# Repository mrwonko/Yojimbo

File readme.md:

# Yojimbo

A Ronin with a new master.

For now, this is just a [work log](log.md) and in-progress designs for a USB-C Probe PCB. I know very little about PCB design, so probably don't use this.

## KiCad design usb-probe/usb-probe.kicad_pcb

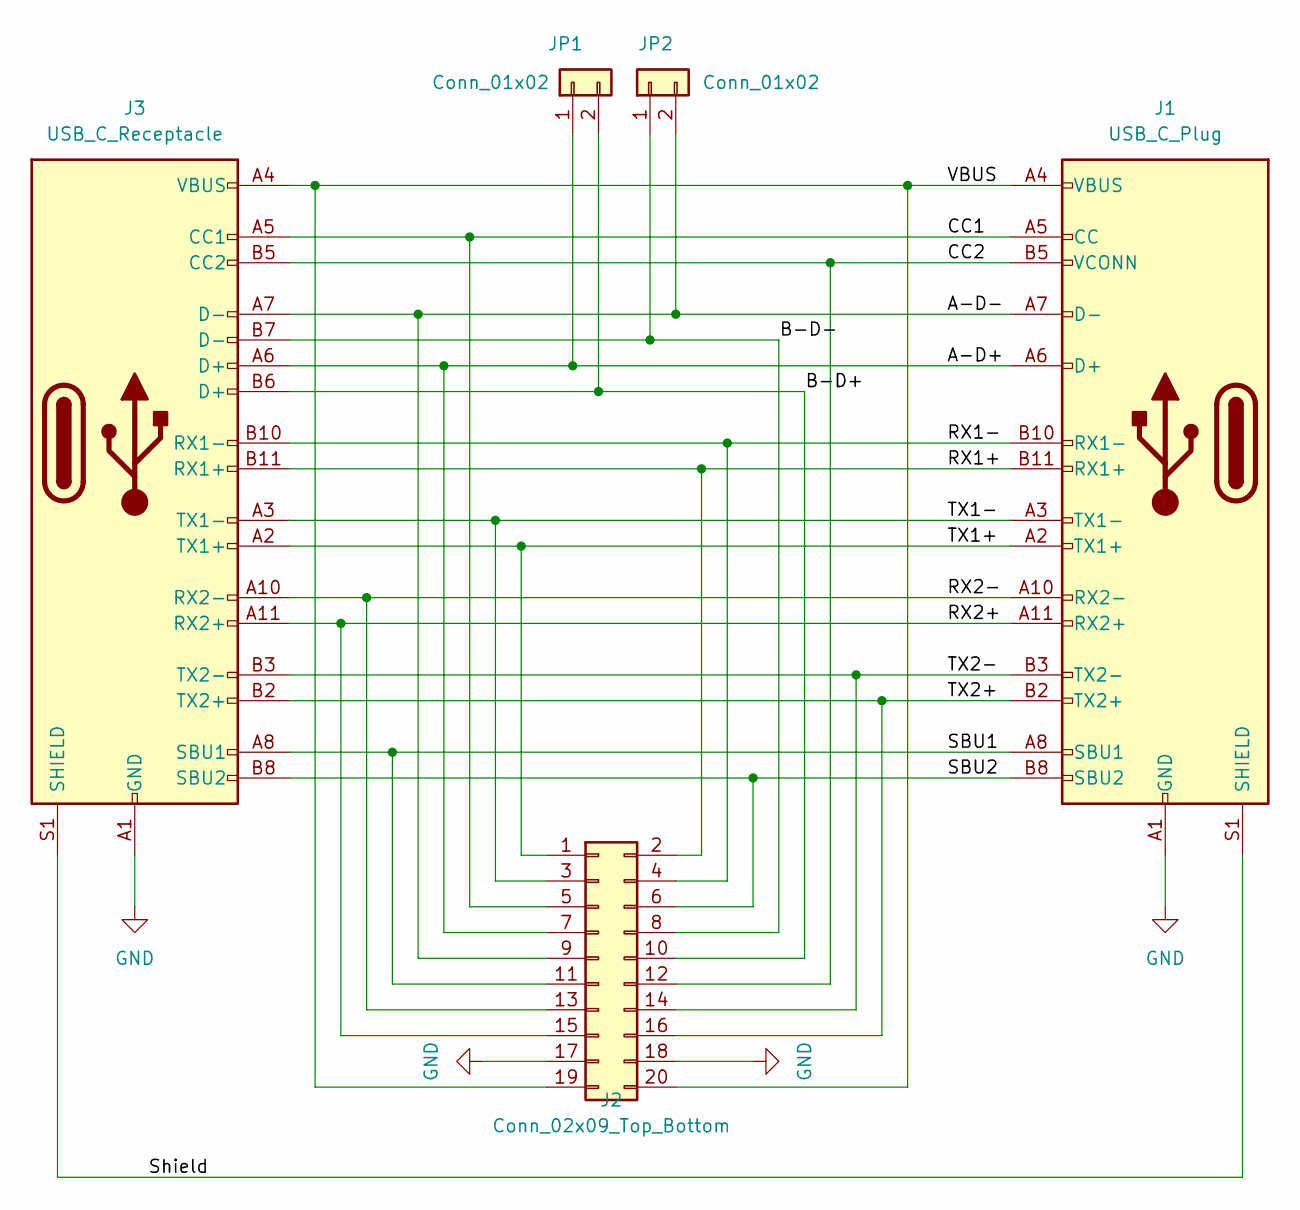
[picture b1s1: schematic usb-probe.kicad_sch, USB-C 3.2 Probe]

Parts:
J1: USB_C_Plug; USB_C_Plug_Molex_105444
J2: Conn_02x09_Top_Bottom; IDC-Header_2x10_P2.54mm_Vertical
J3: USB_C_Receptacle; USB_C_Receptacle_Molex_105450-0101
JP1, JP2: Conn_01x02; PinHeader_1x02_P2.54mm_Vertical

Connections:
/A-D+: J1.A6 (D+), J2.7, J3.A6 (D+), JP1.1
/A-D-: J1.A7 (D-), J2.9, J3.A7 (D-), JP2.2
/B-D+: J2.10, J3.B6 (D+), JP1.2
/B-D-: J2.8, J3.B7 (D-), JP2.1
/CC1: J1.A5 (CC), J2.5, J3.A5 (CC1)
/CC2: J1.B5 (VCONN), J2.12, J3.B5 (CC2)
/RX1+: J1.B11 (RX1+), J2.2, J3.B11 (RX1+)
/RX1-: J1.B10 (RX1-), J2.4, J3.B10 (RX1-)
/RX2+: J1.A11 (RX2+), J2.15, J3.A11 (RX2+)
/RX2-: J1.A10 (RX2-), J2.13, J3.A10 (RX2-)
/SBU1: J1.A8 (SBU1), J2.11, J3.A8 (SBU1)
/SBU2: J1.B8 (SBU2), J2.6, J3.B8 (SBU2)
/Shield: J1.S1 (SHIELD), J3.S1 (SHIELD)
/TX1+: J1.A2 (TX1+), J2.1, J3.A2 (TX1+)
/TX1-: J1.A3 (TX1-), J2.3, J3.A3 (TX1-)
/TX2+: J1.B2 (TX2+), J2.16, J3.B2 (TX2+)
/TX2-: J1.B3 (TX2-), J2.14, J3.B3 (TX2-)
/VBUS: J1.A4 (VBUS), J1.A9 (VBUS), J1.B4 (VBUS), J1.B9 (VBUS), J2.19, J2.20, J3.A4 (VBUS), J3.A9 (VBUS), J3.B4 (VBUS), J3.B9 (VBUS)
GND: J1.A1 (GND), J1.A12 (GND), J1.B1 (GND), J1.B12 (GND), J2.17, J2.18, J3.A1 (GND), J3.A12 (GND), J3.B1 (GND), J3.B12 (GND)

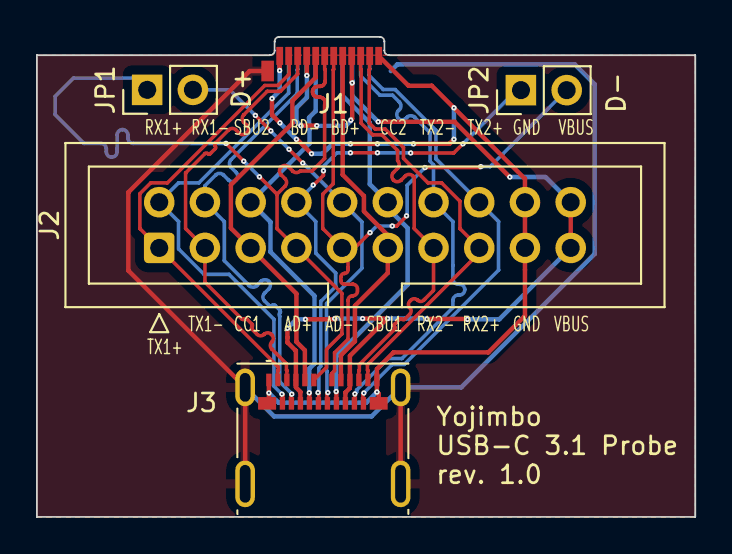
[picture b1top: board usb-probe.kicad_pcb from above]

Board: 2 copper layers, 36.6 x 26.7 mm, 5 parts (0 on the bottom side), 19 nets.

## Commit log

2024-02-14 Add progress log and WIP USB-C Probe design
2024-02-14 Started routing PCB
    And fixed an accidental connection in the schema.
2024-02-14 Added vias for B pin header
2024-02-14 Routed B-side to pin header
2024-02-15 Switched to USB-C Plug
    I learned that USB-C cables have chips that encode their capabilities, so
    putting two in series probably won't work. I've replaced one receptacle with a
    plug.
    I've also changed the pin header to an IDC connector, which should match what
    my logic analyzer uses. By placing it between the USB-C plug and receptacle,
    the routing becomes significantly simpler.
2024-02-17 Disconnect Ground and Shield
    It's up to the connected device to decide what to do with the shield, we just
    need to pass it through.
    Fixes #4
2024-02-17 fiddling around
2024-02-17 Attempt to equalise JP1 and JP2 D+/D- length
    D+ and D- is a differential pair, so the tracks created by shorting JP1 and JP2
    should be of equal length. I used the Python console to determine the track
    lengths:
    import pcbnew
    sum(t.GetLength() for t in pcbnew.GetBoard().GetTracks() if t.IsSelected())
    Which gave me a difference of about 7.2mm. I added another 4*1.6mm due to a
2024-02-25 Add log entry about off-the-shelf usb-c probe
